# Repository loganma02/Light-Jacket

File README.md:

# Light Jacket

In this project I set out to make a jacket for a costume with which I could change colors and pulse lights in a pattern,
[WLED](https://github.com/WLED/WLED) allowed for app-based control and minimal fiddling once powered on.

## <ins>PCB Update Mid May 2026 </ins>

[See it in action here!](https://youtu.be/194a6y9pxL4)
<table>
  <tr>
    <td></td>
    <td></td>
  </tr>
</table>

This revision arrived and looks great with the purple silkscreen. Trying the score and snap proved difficult due to the copper pour over the region, but tin shears made easy work of cutting off the breakout boards.

With the breakout board I made to attach to an addressable strip using USB-C I flipped the power and ground connections from what I intended, I wanted to sandwich the solder between the board and the strip. Nonetheless it feels much sturdier than soldering individual wires cut from the inside of a cable, and looks a lot cleaner too.
The USB-C connector on the board for output works quite well, if I switch away from USB-A I could shrink the vertical footprint too.

The microphone remains to be working even with an added decoupling capacitor near its power input. There is a breakout board where I'll use a different microcontroller to test its function, perhaps it just isn't compatible with WLED as is.

The 5 onboard LEDs available to control came only from having an abundance of GPIO pins leftover, but I find them to be a nice touch. WLED can easily bundle them into a segment to display effects. Perhaps they could be used to show information to justify their placement beyond aesthetics, but even without I think the small increase in BOM cost is worth it.

## <ins>PCB Update Mid April 2026 </ins>
Taking into account some of the problems with the board as it was:
* Addressable LED control not working as expected
* [No resistor on the LED data lines](https://quinled.info/data-signal-cable-conditioning/)
* No testing pads for 5v LED signals
* Microphone not working
* USB-A ports too close together for thick plugs
* UCB-C port in wrong corner for intended use with power bank
* Only one controllable onboard LED
* Unrounded corners

I decided to design another revision, this time in KiCad to further my skills with that software. Using the [LCSC library loader](https://github.com/dsa-t/jlc-kicad-lib-loader) addon bringing footprints and step models from my EasyEDA design was easy, and reconstructing the schematic in KiCad took only a little while.

I realized while designing I wanted breakout boards for testing the microphone on its own, as well as USB-C boards with pads that match the size and layout of the strip. I used mousebites provided by [Panelization.pretty](https://github.com/madworm/Panelization.pretty) to add those breakouts to the side of the main board:

Unfortunately this was rejected by JLCPCB as containing too many individual designs to quality for lower manufacturing costs, likely due to extra care needed in handling panelized boards. I instead decided to make the breakouts contained within the same shape as the main board (which JLCPCB did accept) and will use the score-and-snap method to separate them when it arrives.

<table>
  <tr>
    <td></td>
    <td></td>
  </tr>
</table>

## <ins>PCB Update Early April 2026 </ins>
The first revision of the PCB arrived and came out of JLCPCB fab better than expected. I was a little bit worried about silkscreen readability as text 0.15mm stroke width was ever so slightly below their [manufacturing capabilities](https://jlcpcb.com/capabilities/pcb-capabilities), but it came through perfectly readable.
<table>
  <tr>
    <td></td>
    <td></td>
  </tr>
</table>

Soldering was relatively easy if not time-consuming, as this was my first experience with hor air reflow soldering for SMD components.

Once assembled I could verify that both my 3.3v and 5v power rails were functioning with both LED's lighting up, and went ahead and installed WLED v16 on it through USB. The PWM RGB strip control worked without a hitch, and could drive an LED strip with a common voltage and individual color grounds.

I did run into a problem with addressable strip control where I would get a randomly blinking mess. See it here:
<details> 
  <summary>Caution: Flashing Lights</summary>

</details>

I don't have an oscilloscope to be able to test and see what's happening to the signal, but some research leads me to believe it might have to do with the way I'm using the TXS0108EPWR for level shifting. It seems to be designed more for high-speed onboard signal shifting whose output runs [less than 6 inches](https://learn.sparkfun.com/tutorials/level-shifter---8-channel-txs0108e-hookup-guide/all#:~:text=Signal%20Oscillations,level%20shifters.).
The bi-directionality of the TXS0108EPWR could mean that it's picking up noise on the "output" that triggers it to switch directions and start communicating in the wrong direction.
Letting the supply voltage and ground travel though a USB cable while connecting the data line straight to a 3.3v signal output (which should be too low for the WS2812b) from the ESP32 made it work no problem.

## <ins>PCB Update March 2026 </ins>

Currently awaiting delivery of a prototype PCB board for this jacket. Using an ESP32-S3 and a digital microphone to make audio reactivity possible with WLED.
Chose to use USB-C for programming and power due to availability of cables, and the USB-A plug (but not the full standard) for the connection to the lights. Exploring USB-C plug or magnetic connectors for this purpose.
Gerber files can be found [here](PCB/LightJacketV0.1.zip).

## Jacket Construction

The strip runs hidden along the inside next to the zipper for an ambient lighting effect, and visible around the collar for the exposed design choice.
The battery and circuit board tuck into an existing pocket on the inside.

I decided to sew in the strip for durability rather than use adhesive, and tried to match existing seam lines.

## Circuitry
I used an ESP8266 and a single color RGB LED strip as that's what I had on hand, but opting for a ESP32 increases options available for WLED, and addressable LED strips allow for more impressive patterns to be displayed.
WLED has an option to control single color strips with PWM signals for each RGB channel, and I fed signal each into a transistor to boost the power for that channel.
Power is supplied by a phone battery bank connected by a USB cable spliced to provide 5V to the ESP as well as each transistor. 

*Transistor side of perfboard*

*ESP8266 on perfboard*

## Next steps
I would like to upgrade the microcontroller to an ESP32 and add a microphone, as WLED has better support for audio reactivity on that board.
Ultimately want the jacket to react to sounds, such as pulsing along to the beat of music on a dancefloor, or visually alerting the user to a dangerously loud environment.

## Images

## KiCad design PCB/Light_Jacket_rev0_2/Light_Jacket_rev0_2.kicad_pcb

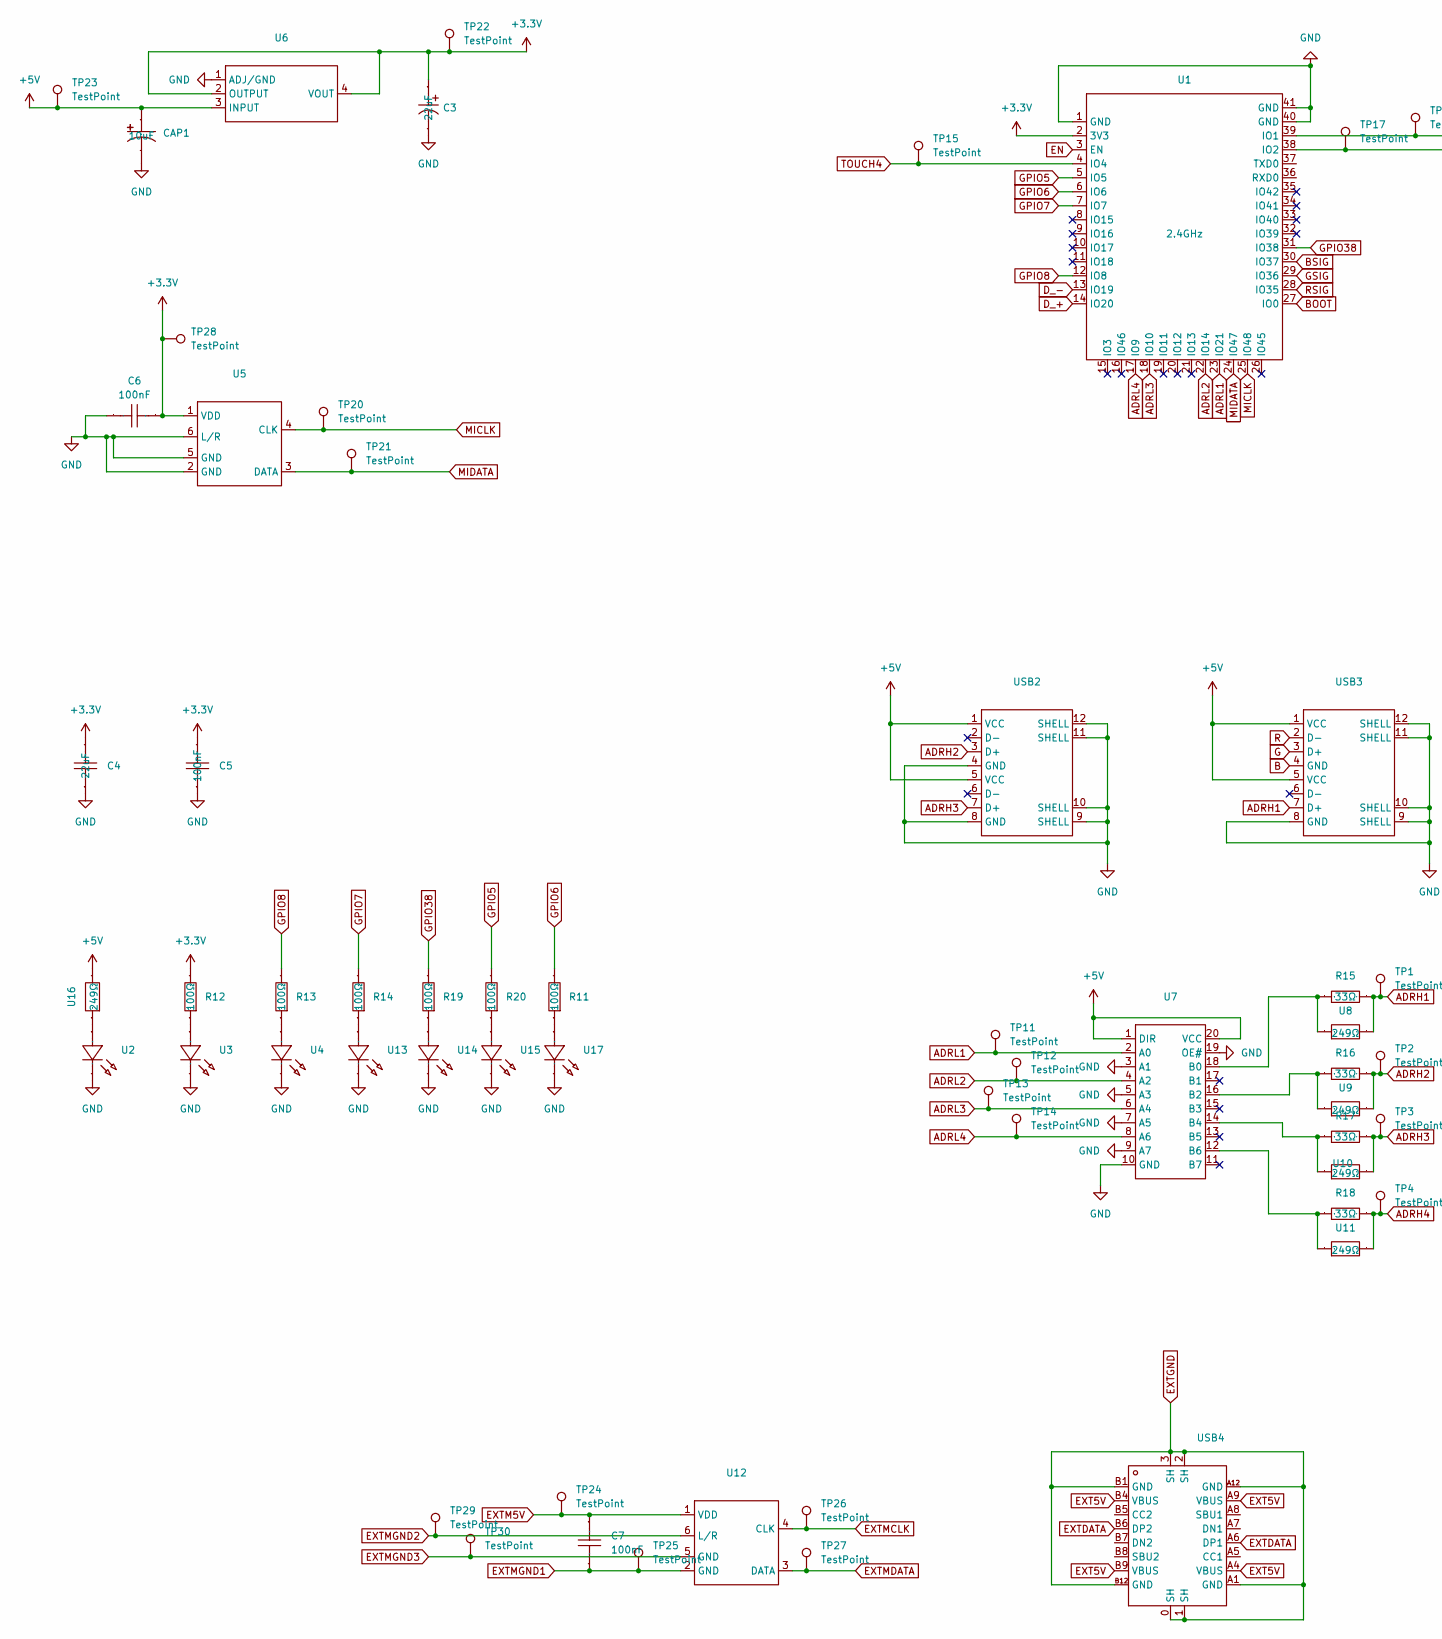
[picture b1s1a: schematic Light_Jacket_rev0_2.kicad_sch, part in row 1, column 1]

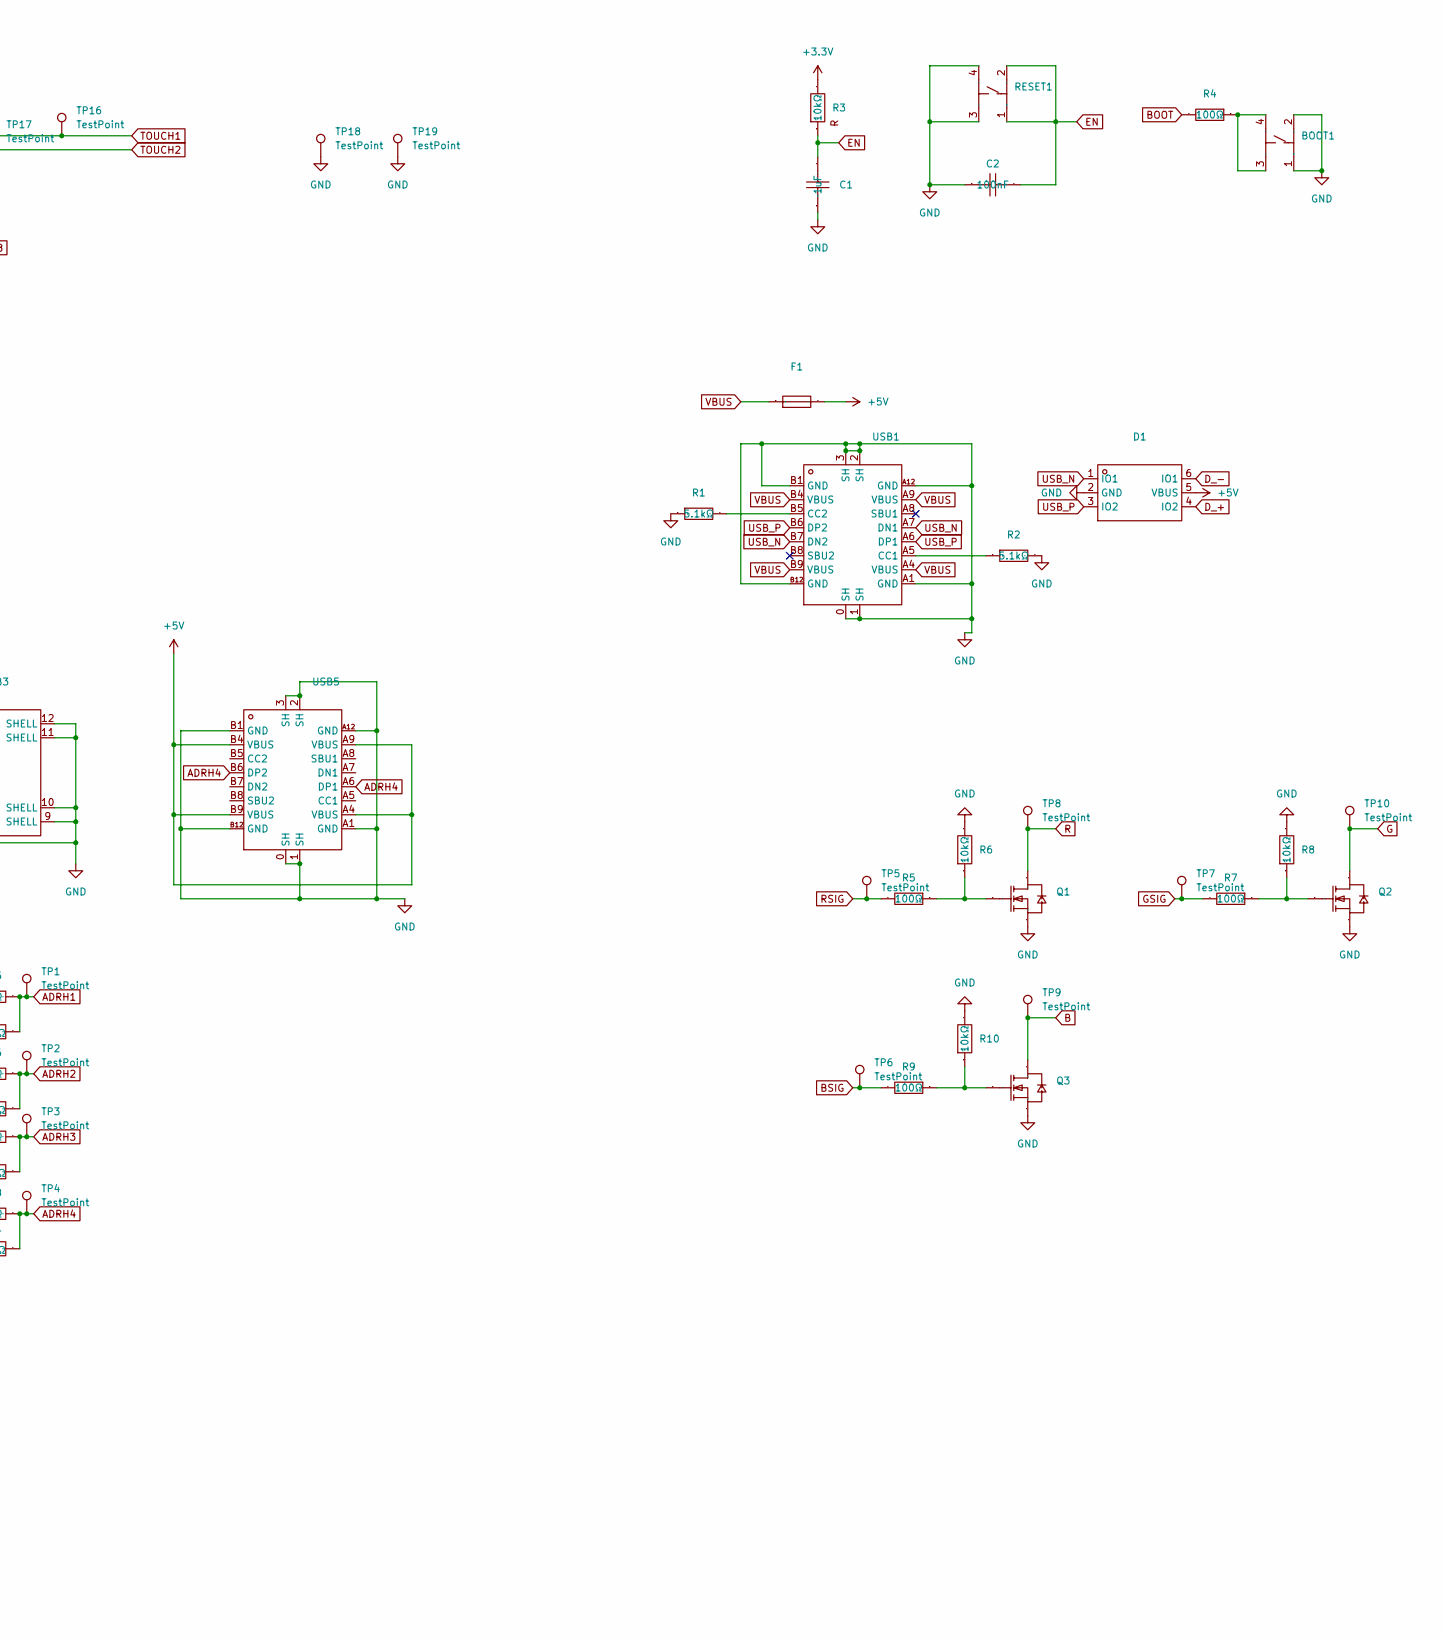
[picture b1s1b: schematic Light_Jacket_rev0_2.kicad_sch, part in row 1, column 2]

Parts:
BOOT1: SW-SMD_4P-L6.0-W6.0-P4.50-LS9.0-H7.3; Manufacturer Part HX-6x6x7.3-TP FT square button; LCSC Part Name 6*6*7.3mm贴片 方头 轻触开关
C1: 1uF; C0603; Manufacturer Part CL10A105KB8NNNC; LCSC Part Name 1uF ±10% 50V
C2, C5, C6, C7: 100nF; C0603; Manufacturer Part CC0603KRX7R9BB104; LCSC Part Name 100nF ±10% 50V
C3: 22uF; CAP-SMD_L3.5-W2.8; Manufacturer Part CA45-B-10V-22uF-K; LCSC Part Name 22uF ±10% 10V
C4: 22uF; C0805; Manufacturer Part CL21A226MAYNNNE; LCSC Part Name 22uF ±20% 25V
CAP1: 10uF; CAP-SMD_L2.0-W1.3-FD; Manufacturer Part CA45-P-10V-10uF-K; LCSC Part Name 10uF ±10% 10V
D1: SOT-23-6_L2.9-W1.6-P0.95-LS2.8-BL; Manufacturer Part USBLC6-2SC6; LCSC Part Name ESD，可防30kV静电
F1: F1812; Manufacturer Part BSMD1812-250-8V; LCSC Part Name 8V 2.5A 1812自恢复
Q1, Q2, Q3: SOT-23-3_L3.0-W1.6-P1.90-LS2.8-BR; Manufacturer Part AO3400A; LCSC Part Name N沟道,电流:5.8A,耐压:30V
R1, R2: 5.1kΩ; R0805; Manufacturer Part 0805W8F5101T5E; LCSC Part Name 5.1kΩ ±1% 125mW 厚膜电阻
R3, R6, R8, R10: 10kΩ; R0603; Manufacturer Part FRC0603J103 TS; LCSC Part Name 10kΩ ±5% 100mW 厚膜电阻
R4, R5, R7, R9, R11, R12, R13, R14, R19, R20: 100Ω; R0603; Manufacturer Part RC0603FR-07100RL; LCSC Part Name 厚膜电阻 100Ω ±1% 100mW
R15, R16, R17, R18: 33Ω; R0603; Manufacturer Part RC0603FR-0733RL; LCSC Part Name 厚膜电阻 33Ω ±1% 100mW
RESET1: SW-SMD_4P-L6.0-W6.0-P4.50-LS9.0-H7.3; Manufacturer Part HX-6x6x7.3-TP FT square button; LCSC Part Name 6*6*7.3mm贴片 方头 轻触开关
TP1, TP2, TP3, TP4, TP5, TP6, TP7, TP8, TP9, TP10, TP11, TP12, TP13, TP14, TP15, TP16, TP17, TP18, TP19, TP20, TP21, TP22, TP23, TP24, TP25, TP26, TP27, TP28, TP29, TP30: TestPoint; EasyEDA Pad
U1: 2.4GHz; WIRELM-SMD_ESP32-S3-WROOM-1; Manufacturer Part ESP32-S3-WROOM-1-N16R2; LCSC Part Name 不带固件 通用型Wi-Fi+低功耗蓝牙MCU模组
U2, U3, U4, U13, U14, U15, U17: LED0603-FD; Manufacturer Part YLED0603G; LCSC Part Name 翠绿色 独立二极管
U5, U12: MIC-SMD_6P-L4.0-W2.0_LMD4020T261-OC3; Manufacturer Part MSM261DGT003; LCSC Part Name 1.8V 26dB
U6: SOT-223-3_L6.5-W3.4-P2.30-LS7.0-BR; Manufacturer Part AMS1117-3.3; LCSC Part Name 1A低压差线性稳压器
U7: TSSOP-20_L6.5-W4.4-P0.65-LS6.4-BL; Manufacturer Part 74HCT245PW; LCSC Part Name 74HCT245PW
U8, U9, U10, U11, U16: 249Ω; R0603; Manufacturer Part FRC0603F2490TS; LCSC Part Name 249Ω ±1% 100mW 厚膜电阻
USB1, USB4, USB5: USB-C_SMD-TYPE-C-31-M-12; Manufacturer Part USB-TYPE-C-018; LCSC Part Name Type-C 母 卧贴
USB2, USB3: USB-A-TH_AF-SS-JB17.6; Manufacturer Part AF SS-JB17.6; LCSC Part Name Type-A弯插双层母座

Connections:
+3.3V: C3.1, C4.2, C5.2, C6.1, R3.2, R12.2, TP22.1, TP28.1, U1.2 (3V3), U5.1 (VDD), U6.2 (OUTPUT), U6.4 (VOUT)
+5V: CAP1.1, D1.5 (VBUS), F1.2, TP23.1, U6.3 (INPUT), U7.1 (DIR), U7.20 (VCC), U16.2, USB2.1 (VCC), USB2.5 (VCC), USB3.1 (VCC), USB3.5 (VCC), USB5.A4 (VBUS), USB5.A9 (VBUS), USB5.B4 (VBUS), USB5.B9 (VBUS)
ADRH1: R15.2, TP1.1, U8.2, USB3.7 (D+)
ADRH2: R16.2, TP2.1, U9.2, USB2.3 (D+)
ADRH3: R17.2, TP3.1, U10.2, USB2.7 (D+)
ADRH4: R18.2, TP4.1, U11.2, USB5.A6 (DP1), USB5.B6 (DP2)
ADRL1: TP11.1, U1.23 (IO21), U7.2 (A0)
ADRL2: TP12.1, U1.22 (IO14), U7.4 (A2)
ADRL3: TP13.1, U1.18 (IO10), U7.6 (A4)
ADRL4: TP14.1, U1.17 (IO9), U7.8 (A6)
B: Q3.3 (D), TP9.1, USB3.4 (GND)
BOOT: R4.2, U1.27 (IO0)
BSIG: R9.2, TP6.1, U1.30 (IO37)
D_+: D1.4 (IO2), U1.14 (IO20)
D_-: D1.6 (IO1), U1.13 (IO19)
EN: C1.2, C2.2, R3.1, RESET1.1 (A), RESET1.2 (B), U1.3 (EN)
EXT5V: USB4.A4 (VBUS), USB4.A9 (VBUS), USB4.B4 (VBUS), USB4.B9 (VBUS); also elsewhere on the board
EXTDATA: USB4.A6 (DP1), USB4.B6 (DP2); also elsewhere on the board
EXTGND: USB4.0 (SH), USB4.1 (SH), USB4.2 (SH), USB4.3 (SH), USB4.A1 (GND), USB4.A12 (GND), USB4.B1 (GND), USB4.B12 (GND); also elsewhere on the board
EXTM5V: C7.1, TP24.1, U12.1 (VDD)
EXTMCLK: TP26.1, U12.4 (CLK)
EXTMDATA: TP27.1, U12.3 (DATA)
EXTMGND1: C7.2, TP25.1, U12.2 (GND)
EXTMGND2: TP29.1, U12.6 (L/R)
EXTMGND3: TP30.1, U12.5 (GND)
G: Q2.3 (D), TP10.1, USB3.3 (D+)
GND: BOOT1.1 (A), BOOT1.2 (B), C1.1, C2.1, C3.2, C4.1, C5.1, C6.2, CAP1.2, D1.2 (GND), Q1.2 (S), Q2.2 (S), Q3.2 (S), R1.1, R2.2, R6.2, R8.2, R10.2, RESET1.3 (C), RESET1.4 (D), TP18.1, TP19.1, U1.1 (GND), U1.40 (GND), U1.41 (GND), U2.2 (-), U3.2 (-), U4.2 (-), U5.2 (GND), U5.5 (GND), U5.6 (L/R), U6.1 (ADJ/GND), U7.3 (A1), U7.5 (A3), U7.7 (A5), U7.9 (A7), U7.10 (GND), U7.19 (OE#), U13.2 (-), U14.2 (-), U15.2 (-), U17.2 (-), USB1.0 (SH), USB1.1 (SH), USB1.2 (SH), USB1.3 (SH), USB1.A1 (GND), USB1.A12 (GND), USB1.B1 (GND), USB1.B12 (GND), USB2.4 (GND), USB2.8 (GND), USB2.9 (SHELL), USB2.10 (SHELL), USB2.11 (SHELL), USB2.12 (SHELL), USB3.8 (GND), USB3.9 (SHELL), USB3.10 (SHELL), USB3.11 (SHELL), USB3.12 (SHELL), USB5.0 (SH), USB5.1 (SH), USB5.2 (SH), USB5.3 (SH), USB5.A1 (GND), USB5.A12 (GND), USB5.B1 (GND), USB5.B12 (GND)
GPIO5: R20.2, U1.5 (IO5)
GPIO6: R11.2, U1.6 (IO6)
GPIO7: R14.2, U1.7 (IO7)
GPIO8: R13.2, U1.12 (IO8)
GPIO38: R19.2, U1.31 (IO38)
GSIG: R7.2, TP7.1, U1.29 (IO36)
MICLK: TP20.1, U1.25 (IO48), U5.4 (CLK)
MIDATA: TP21.1, U1.24 (IO47), U5.3 (DATA)
unnamed: BOOT1.3 (C), BOOT1.4 (D), R4.1
unnamed: Q1.1 (G), R5.1, R6.1
unnamed: Q2.1 (G), R7.1, R8.1
unnamed: Q3.1 (G), R9.1, R10.1
unnamed: U2.1 (+), U16.1
unnamed: R12.1, U3.1 (+)
unnamed: R13.1, U4.1 (+)
unnamed: R15.1, U7.18 (B0), U8.1
unnamed: R16.1, U7.16 (B2), U9.1
unnamed: R17.1, U7.14 (B4), U10.1
unnamed: R18.1, U7.12 (B6), U11.1
unnamed: R14.1, U13.1 (+)
unnamed: R19.1, U14.1 (+)
unnamed: R20.1, U15.1 (+)
unnamed: R11.1, U17.1 (+)
unnamed: R2.1, USB1.A5 (CC1)
unnamed: R1.2, USB1.B5 (CC2)
R: Q1.3 (D), TP8.1, USB3.2 (D-)
RSIG: R5.2, TP5.1, U1.28 (IO35)
TOUCH1: TP16.1, U1.39 (IO1)
TOUCH2: TP17.1, U1.38 (IO2)
TOUCH4: TP15.1, U1.4 (IO4)
USB_N: D1.1 (IO1), USB1.A7 (DN1), USB1.B7 (DN2)
USB_P: D1.3 (IO2), USB1.A6 (DP1), USB1.B6 (DP2)
VBUS: F1.1, USB1.A4 (VBUS), USB1.A9 (VBUS), USB1.B4 (VBUS), USB1.B9 (VBUS)

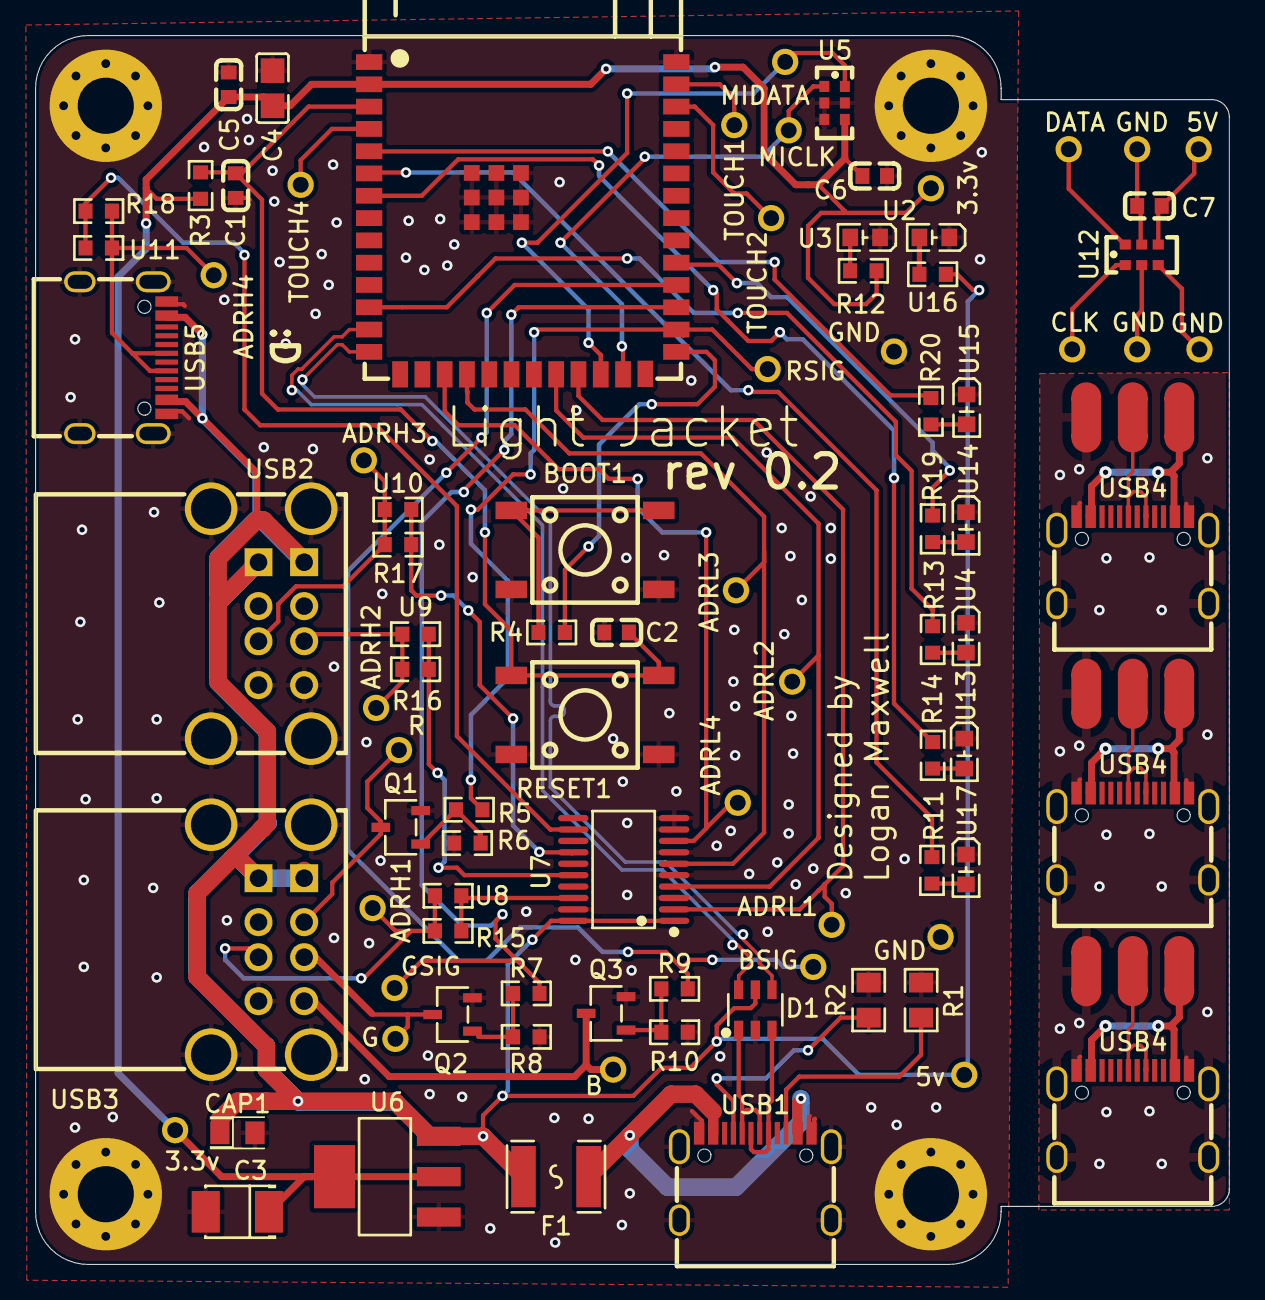
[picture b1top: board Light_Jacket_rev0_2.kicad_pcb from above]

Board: 2 copper layers, 68.0 x 70.0 mm, 89 parts (0 on the bottom side), 60 nets.

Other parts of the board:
USB4#2, USB4#3: USB-C_SMD-TYPE-C-31-M-12

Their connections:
EXT5V: USB4#2.A4 (VBUS), USB4#2.A9 (VBUS), USB4#2.B4 (VBUS), USB4#2.B9 (VBUS), USB4#3.A4 (VBUS), USB4#3.A9 (VBUS), USB4#3.B4 (VBUS), USB4#3.B9 (VBUS); also elsewhere on the board
EXTDATA: USB4#2.A6 (DP1), USB4#2.B6 (DP2), USB4#3.A6 (DP1), USB4#3.B6 (DP2); also elsewhere on the board
EXTGND: USB4#2.0 (SH), USB4#2.1 (SH), USB4#2.2 (SH), USB4#2.3 (SH), USB4#2.A1 (GND), USB4#2.A12 (GND), USB4#2.B1 (GND), USB4#2.B12 (GND), USB4#3.0 (SH), USB4#3.1 (SH), USB4#3.2 (SH), USB4#3.3 (SH), USB4#3.A1 (GND), USB4#3.A12 (GND), USB4#3.B1 (GND), USB4#3.B12 (GND); also elsewhere on the board

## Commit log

2026-03-17 Added v0.1 pcb files and images
2026-03-17 Removed duplicate image open jacket
2026-04-22 Added readme entries for early and late april. Also changed structure of PCB folder
2026-04-25 Testing table for readme
2026-04-25 Adding another table for first revision board
2026-05-18 PCB update mid may
